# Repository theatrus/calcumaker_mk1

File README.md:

# Calcumaker - Desktop LED calculator

A desktop calculator design chock full of seven segment LEDs and
powered by an Atmel AVR xMega.

Calculate on your desktop with style.

The keypad was designed to support RPN-style "big enter button" layouts.

# Features

 * 7 segment LEDs!
 * Buttons!
 * A processor!

# License

The CERN OHL License 1.2 is used. Please see the accompanying
LICENSE.txt file.

# Design Status

This design was never built. Its intent is to inspire others to make
equally exciting and silly projects.

The BOM is *incomplete*.

# Files available

The original design is available as Eagle 6.x (XML-based) design
files, in the eagle/ directory.

Gerber files from the Eagle board file are made available in the
gerber/ directory.

Schematic PDF is available in the root of this repository.

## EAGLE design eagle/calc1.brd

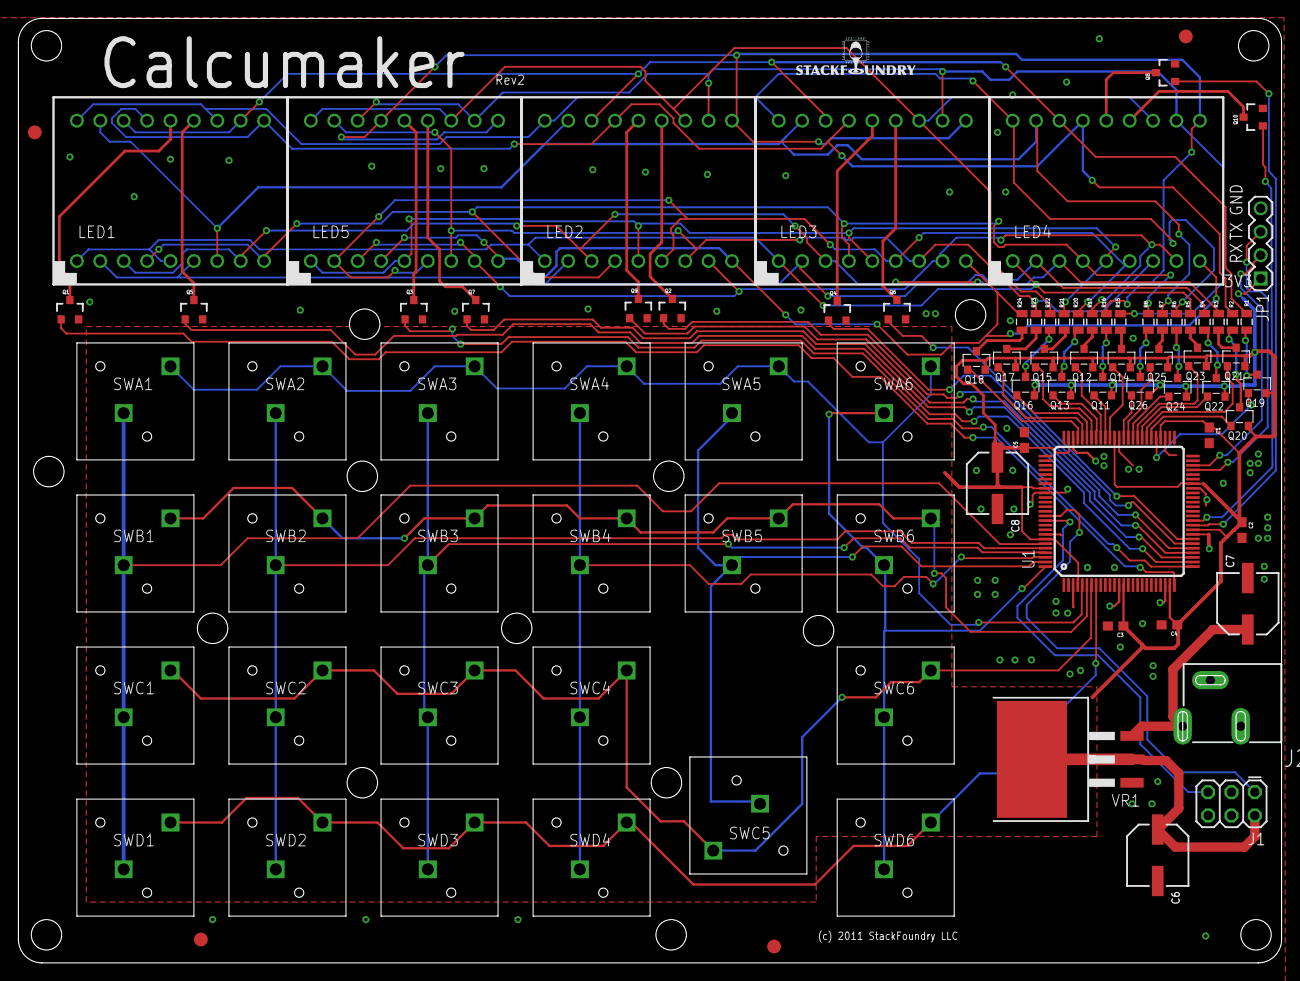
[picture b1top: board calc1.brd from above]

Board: 2 copper layers, 137.1 x 102.5 mm, 103 parts (0 on the bottom side), 85 nets.

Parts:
$2_80_$: FIDUCIAL1.5X3; FIDUCIAL-1.5X3
$2_85_$: STAND-OFF
C1, C2, C3, C4, C5: 0.1uf; 0603
C6, C7, C8: CSV-D
J1: AVR_PDI; 2X3
J2: POWER_JACKSLT; POWER_JACK_SLOT
JP1: 1X04
LED1, LED2, LED3, LED4, LED5: 2X7SEGMENT2X; 2X7SEG_PTH
LOGO1: SFLOGO
Q1, Q2, Q3, Q4, Q5, Q6, Q7, Q8, Q9, Q10: SOT23-3
Q11, Q12, Q13, Q14, Q15, Q16, Q17, Q18, Q19, Q20, Q21, Q22, Q23, Q24, Q25, Q26: SOT23
R1, R2, R3, R4, R5, R6, R7, R8, R15, R16, R17, R20, R21, R22, R23, R24: 10; 0805
SWA1, SWA2, SWA3, SWA4, SWA5, SWA6: 320E1-1
SWB1, SWB2, SWB3, SWB4, SWB5, SWB6: 320E1-1
SWC1, SWC2, SWC3, SWC4, SWC5, SWC6: 320E1-1
SWD1, SWD2, SWD3, SWD4, SWD6: 320E1-1
U1: XMEGA-A1-100TQFP; TQFP100
U$1, U$5, U$6, U$7, U$8, U$10, U$11, U$12, U$13, U$15, U$16, U$17, U$18, U$19: STAND-OFF
U$2, U$3, U$4: FIDUCIAL1.5X3; FIDUCIAL-1.5X3
VR1: LM1086VR; TO263

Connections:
+3V3: C1.1, C2.1, C3.1, C4.1, C5.1, C6.+, C8.+, J1.2, JP1.1, Q11.2, Q12.2, Q13.2, Q14.2, Q15.2, Q16.2, Q17.2, Q18.2, Q19.2, Q20.2, Q21.2, Q22.2, Q23.2, Q24.2, Q25.2, Q26.2, U1.4, U1.14, U1.24, U1.34, U1.44, U1.54, U1.64, U1.74, U1.83, U1.94, VR1.2, VR1.TAB
+5V: C7.+, J2.PWR, VR1.3
COL1: SWA1.P$1, SWB1.P$1, SWC1.P$1, SWD1.P$1, U1.95
COL2: SWA2.P$1, SWB2.P$1, SWC2.P$1, SWD2.P$1, U1.96
COL3: SWA3.P$1, SWB3.P$1, SWC3.P$1, SWD3.P$1, U1.97
COL4: SWA4.P$1, SWB4.P$1, SWC4.P$1, SWD4.P$1, U1.98
COL5: SWA5.P$1, SWB5.P$1, SWC5.P$1, U1.99
COL6: SWA6.P$1, SWB6.P$1, SWC6.P$1, SWD6.P$1, U1.100
DIGA0: LED1.11, LED1.16, LED2.16, LED3.16, LED4.16, R1.2
DIGA1: LED1.10, LED1.15, LED2.15, LED3.15, LED4.15, R2.2
DIGA2: LED1.3, LED1.8, LED2.3, LED3.3, LED4.3, R3.2
DIGA3: LED1.2, LED1.6, LED2.2, LED3.2, LED4.2, R4.2
DIGA4: LED1.1, LED1.5, LED2.1, LED3.1, LED4.1, R5.2
DIGA5: LED1.12, LED1.18, LED2.18, LED3.18, LED4.18, R6.2
DIGA6: LED1.7, LED1.17, LED2.17, LED3.17, LED4.17, R7.2
DIGA7: LED1.4, LED1.9, LED2.4, LED3.4, LED4.4, R8.2
DIGAG0: Q19.1, U1.55
DIGAG1: Q20.1, U1.56
DIGAG2: Q21.1, U1.57
DIGAG3: Q22.1, U1.58
DIGAG4: Q23.1, U1.59
DIGAG5: Q24.1, U1.60
DIGAG6: Q25.1, U1.61
DIGAG7: Q26.1, U1.62
DIGAP0: Q19.3, R1.1
DIGAP1: Q20.3, R2.1
DIGAP2: Q21.3, R3.1
DIGAP3: Q22.3, R4.1
DIGAP4: Q23.3, R5.1
DIGAP5: Q24.3, R6.1
DIGAP6: Q25.3, R7.1
DIGAP7: Q26.3, R8.1
DIGB0: LED2.11, LED3.11, LED4.11, LED5.11, LED5.16, R15.2
DIGB1: LED2.10, LED3.10, LED4.10, LED5.10, LED5.15, R16.2
DIGB2: LED2.8, LED3.8, LED4.8, LED5.3, LED5.8, R17.2
DIGB3: LED2.6, LED3.6, LED4.6, LED5.2, LED5.6, R20.2
DIGB4: LED2.5, LED3.5, LED4.5, LED5.1, LED5.5, R21.2
DIGB5: LED2.12, LED3.12, LED4.12, LED5.12, LED5.18, R22.2
DIGB6: LED2.7, LED3.7, LED4.7, LED5.7, LED5.17, R23.2
DIGB7: LED2.9, LED3.9, LED4.9, LED5.4, LED5.9, R24.2
DIGBG0: Q14.1, U1.65
DIGBG1: Q11.1, U1.66
DIGBG2: Q12.1, U1.67
DIGBG3: Q13.1, U1.68
DIGBG4: Q15.1, U1.69
DIGBG5: Q16.1, U1.70
DIGBG6: Q17.1, U1.71
DIGBG7: Q18.1, U1.72
DIGBP0: Q14.3, R15.1
DIGBP1: Q11.3, R16.1
DIGBP2: Q12.3, R17.1
DIGBP3: Q13.3, R20.1
DIGBP4: Q15.3, R21.1
DIGBP5: Q16.3, R22.1
DIGBP6: Q17.3, R23.1
DIGBP7: Q18.3, R24.1
GND: C1.2, C2.2, C3.2, C4.2, C5.2, C6.-, C7.-, C8.-, J1.6, J2.GND@1, J2.GND@2, JP1.4, Q1.2, Q2.2, Q3.2, Q4.2, Q5.2, Q6.2, Q7.2, Q8.2, Q9.2, Q10.2, U1.3, U1.13, U1.23, U1.33, U1.43, U1.53, U1.63, U1.73, U1.84, U1.93, VR1.1
unnamed: J1.1, U1.89
unnamed: J1.5, U1.90
ROWA: SWA1.P$2, SWA2.P$2, SWA3.P$2, SWA4.P$2, SWA5.P$2, SWA6.P$2, U1.5
ROWB: SWB1.P$2, SWB2.P$2, SWB3.P$2, SWB4.P$2, SWB5.P$2, SWB6.P$2, U1.6
ROWC: SWC1.P$2, SWC2.P$2, SWC3.P$2, SWC4.P$2, SWC5.P$2, SWC6.P$2, U1.7
ROWD: SWD1.P$2, SWD2.P$2, SWD3.P$2, SWD4.P$2, SWD6.P$2, U1.8
RXD: JP1.3, U1.47
SEGC0: LED1.14, Q1.3
SEGC1: LED5.14, Q3.3
SEGC2: LED1.13, Q5.3
SEGC3: LED5.13, Q7.3
SEGC4: LED2.14, Q9.3
SEGC5: LED2.13, Q2.3
SEGC6: LED3.14, Q4.3
SEGC7: LED3.13, Q6.3
SEGC8: LED4.14, Q8.3
SEGC9: LED4.13, Q10.3
SEGG0: Q1.1, U1.25
SEGG1: Q3.1, U1.26
SEGG2: Q5.1, U1.27
SEGG3: Q7.1, U1.28
SEGG4: Q9.1, U1.29
SEGG5: Q2.1, U1.30
SEGG6: Q4.1, U1.31
SEGG7: Q6.1, U1.32
SEGG8: Q8.1, U1.35
SEGG9: Q10.1, U1.36
TXD: JP1.2, U1.48

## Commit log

2009-07-15 Ebecus 1 is born
2009-07-15 Exhale
2009-07-16 Start schematic capture on MCU
2009-07-16 Calc1
2010-07-15 Update to XMEGA128A1
2010-08-19 XMega conversion
2010-08-19 Route signals
2014-04-11 Gerbers and rearrange
2014-04-11 CERN License
2014-04-11 Readme file
2014-04-11 Fix URL

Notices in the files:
eagle/calc1.brd:
(c) 2011 StackFoundry LLC
